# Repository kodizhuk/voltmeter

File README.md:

# Voltmeter for the power supply
Simple voltmeter on the DA14858 microcontroller

## Short description
The three channels ADC are used to measure voltage, current and the potentiometer value (that changed the current limit). The voltage and current are displayed if the potentiometer value isn't changing. If the potentiomter values is changed, the current limit value is displayed instead of the current.

## Schematic
PCB is created using KiKad software

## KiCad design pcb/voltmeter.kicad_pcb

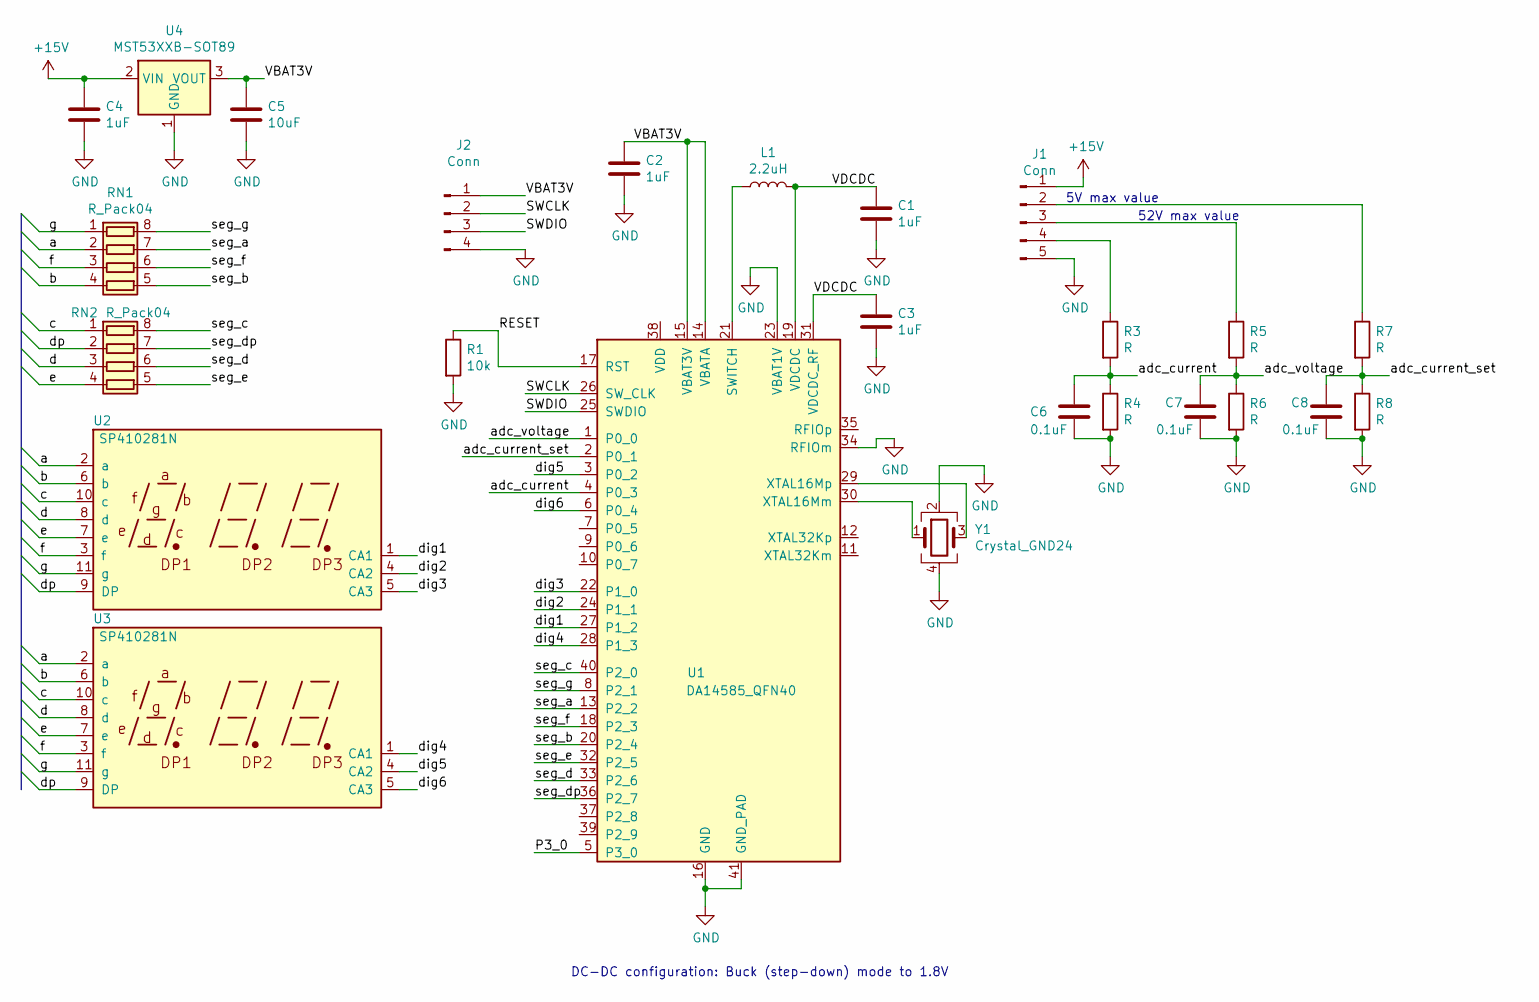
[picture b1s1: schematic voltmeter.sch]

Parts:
C1, C2, C3, C4: 1uF; C_0805_2012Metric_Pad1.18x1.45mm_HandSolder
C5: 10uF; C_0805_2012Metric_Pad1.18x1.45mm_HandSolder
C6, C7, C8: 0.1uF; C_0805_2012Metric_Pad1.18x1.45mm_HandSolder
J1: Conn; PinSocket_1x05_P2.54mm_Vertical
J2: Conn; PinSocket_1x04_P2.54mm_Vertical
L1: 2.2uH; L_0805_2012Metric_Pad1.15x1.40mm_HandSolder
R1: 10k; R_0805_2012Metric_Pad1.20x1.40mm_HandSolder
R3, R4, R5, R6, R7, R8: R; R_0805_2012Metric_Pad1.20x1.40mm_HandSolder
RN1, RN2: R_Pack04; R_Array_Concave_4x0603
U1: DA14585_QFN40; QFN-40-1EP_5x5mm_P0.4mm_EP3.8x3.8mm
U2, U3: SP410281N; 7_seg_0.28in_display
U4: MST53XXB-SOT89; SOT-89-3
Y1: Crystal_GND24; Crystal_SMD_3225-4Pin_3.2x2.5mm

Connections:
+15V: C4.1, J1.1, U4.2 (VIN)
/P3_0: U1.5 (P3_0)
/RESET: R1.1, U1.17 (RST)
/SWCLK: J2.2, U1.26 (SW_CLK)
/SWDIO: J2.3, U1.25 (SWDIO)
/VBAT3V: C2.1, C5.1, J2.1, U1.14 (VBATA), U1.15 (VBAT3V), U4.3 (VOUT)
/VDCDC: C1.1, C3.1, L1.2, U1.19 (VDCDC), U1.31 (VDCDC_RF)
/a: RN1.2 (R2.1), U2.2 (a), U3.2 (a)
/adc_current: C6.1, R3.2, R4.1, U1.4 (P0_3)
/adc_current_set: C8.1, R7.2, R8.1, U1.2 (P0_1)
/adc_voltage: C7.1, R5.2, R6.1, U1.1 (P0_0)
/b: RN1.4 (R4.1), U2.6 (b), U3.6 (b)
/c: RN2.1 (R1.1), U2.10 (c), U3.10 (c)
/d: RN2.3 (R3.1), U2.8 (d), U3.8 (d)
/dig1: U1.27 (P1_2), U2.1 (CA1)
/dig2: U1.24 (P1_1), U2.4 (CA2)
/dig3: U1.22 (P1_0), U2.5 (CA3)
/dig4: U1.28 (P1_3), U3.1 (CA1)
/dig5: U1.3 (P0_2), U3.4 (CA2)
/dig6: U1.6 (P0_4), U3.5 (CA3)
/dp: RN2.2 (R2.1), U2.9 (DP), U3.9 (DP)
/e: RN2.4 (R4.1), U2.7 (e), U3.7 (e)
/f: RN1.3 (R3.1), U2.3 (f), U3.3 (f)
/g: RN1.1 (R1.1), U2.11 (g), U3.11 (g)
/seg_a: RN1.7 (R2.2), U1.13 (P2_2)
/seg_b: RN1.5 (R4.2), U1.20 (P2_4)
/seg_c: RN2.8 (R1.2), U1.40 (P2_0)
/seg_d: RN2.6 (R3.2), U1.33 (P2_6)
/seg_dp: RN2.7 (R2.2), U1.36 (P2_7)
/seg_e: RN2.5 (R4.2), U1.32 (P2_5)
/seg_f: RN1.6 (R3.2), U1.18 (P2_3)
/seg_g: RN1.8 (R1.2), U1.8 (P2_1)
GND: C1.2, C2.2, C3.2, C4.2, C5.2, C6.2, C7.2, C8.2, J1.5, J2.4, R1.2, R4.2, R6.2, R8.2, U1.16 (GND), U1.23 (VBAT1V), U1.34 (RFIOm), U1.41 (GND_PAD), U4.1 (GND), Y1.2, Y1.4
unnamed: J1.2, R7.1
unnamed: J1.3, R5.1
unnamed: J1.4, R3.1
unnamed: L1.1, U1.21 (SWITCH)
unnamed: U1.29 (XTAL16Mp), Y1.3
unnamed: U1.30 (XTAL16Mm), Y1.1

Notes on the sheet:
DC-DC configuration: Buck (step-down) mode to 1.8V
5V max value
52V max value

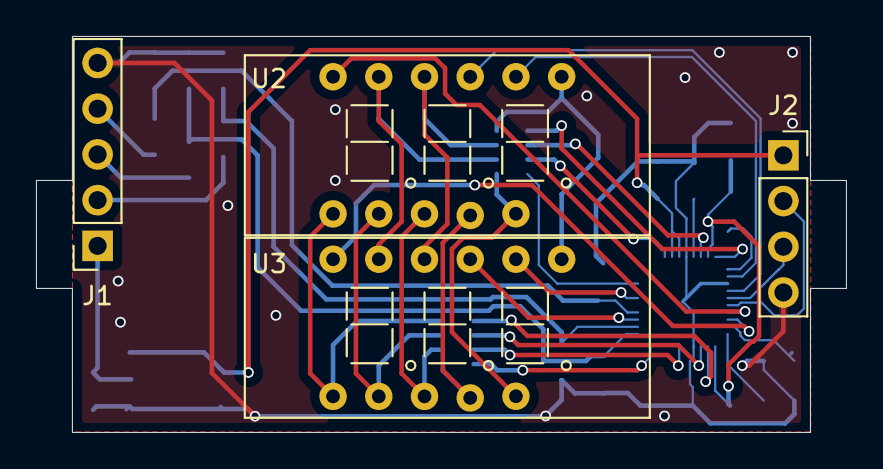
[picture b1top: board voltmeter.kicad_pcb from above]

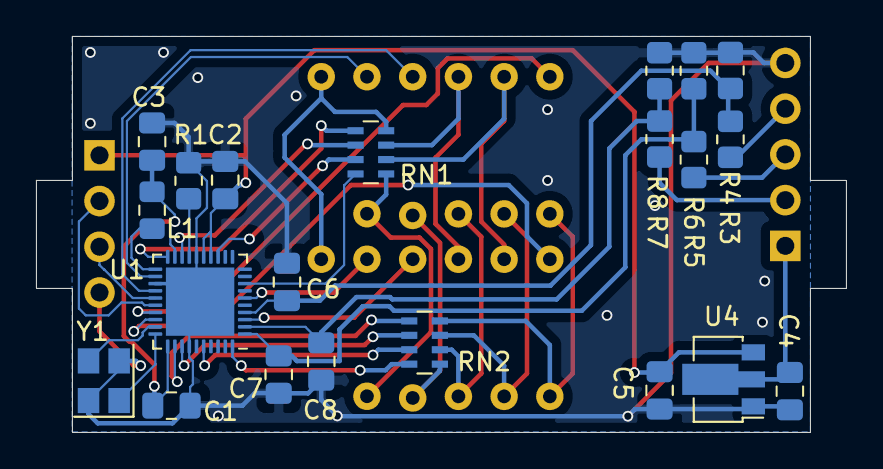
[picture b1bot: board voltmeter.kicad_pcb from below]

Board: 2 copper layers, 45.0 x 22.0 mm, 25 parts (21 on the bottom side), 38 nets.

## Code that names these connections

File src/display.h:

#ifndef DISPLAY

#define DISPLAY
#include "stdint.h"
#include "gpio.h"

//segments, J7 connector
// segA  - P2_2
// segB  - P2_4
// segC  - P2_0
// segD  - P2_6-
// segE  - P2_5-
// segF  - P2_3
// segG  - P2_1
// segDP - P2_7
#define PORT_SEGMENT GPIO_PORT_2
#define PIN_A GPIO_PIN_2
#define PIN_B GPIO_PIN_4
#define PIN_C GPIO_PIN_0
#define PIN_D GPIO_PIN_6
#define PIN_E GPIO_PIN_5
#define PIN_F GPIO_PIN_3
#define PIN_G GPIO_PIN_1
#define PIN_DP GPIO_PIN_7

//digits
// dig0 - P1_2
// dig1 - P1_1
// dig2 - P1_0
// dig3 - P1_3
// dig4 - P0_2
// dig5 - P0_4
#define PORT_DIG0 GPIO_PORT_1
#define PIN_DIG0 GPIO_PIN_2
#define PORT_DIG1 GPIO_PORT_1
#define PIN_DIG1 GPIO_PIN_1
#define PORT_DIG2 GPIO_PORT_1
#define PIN_DIG2 GPIO_PIN_0
#define PORT_DIG3 GPIO_PORT_1
#define PIN_DIG3 GPIO_PIN_3
#define PORT_DIG4 GPIO_PORT_0
#define PIN_DIG4 GPIO_PIN_2
#define PORT_DIG5 GPIO_PORT_0
#define PIN_DIG5 GPIO_PIN_4

void display_init(void);
void display_update(float num1, float num2);

#endif

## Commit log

2023-03-08 add files via upload
    add existing files
2023-03-08 add photos
2023-03-08 add pcb files
2023-03-08 add schematic
2023-03-08 add pcb
2023-03-08 added pcb
2023-03-10 add back and front 3d img
2023-03-10 changed photo to 3d images
2023-03-10 add 3d from img
